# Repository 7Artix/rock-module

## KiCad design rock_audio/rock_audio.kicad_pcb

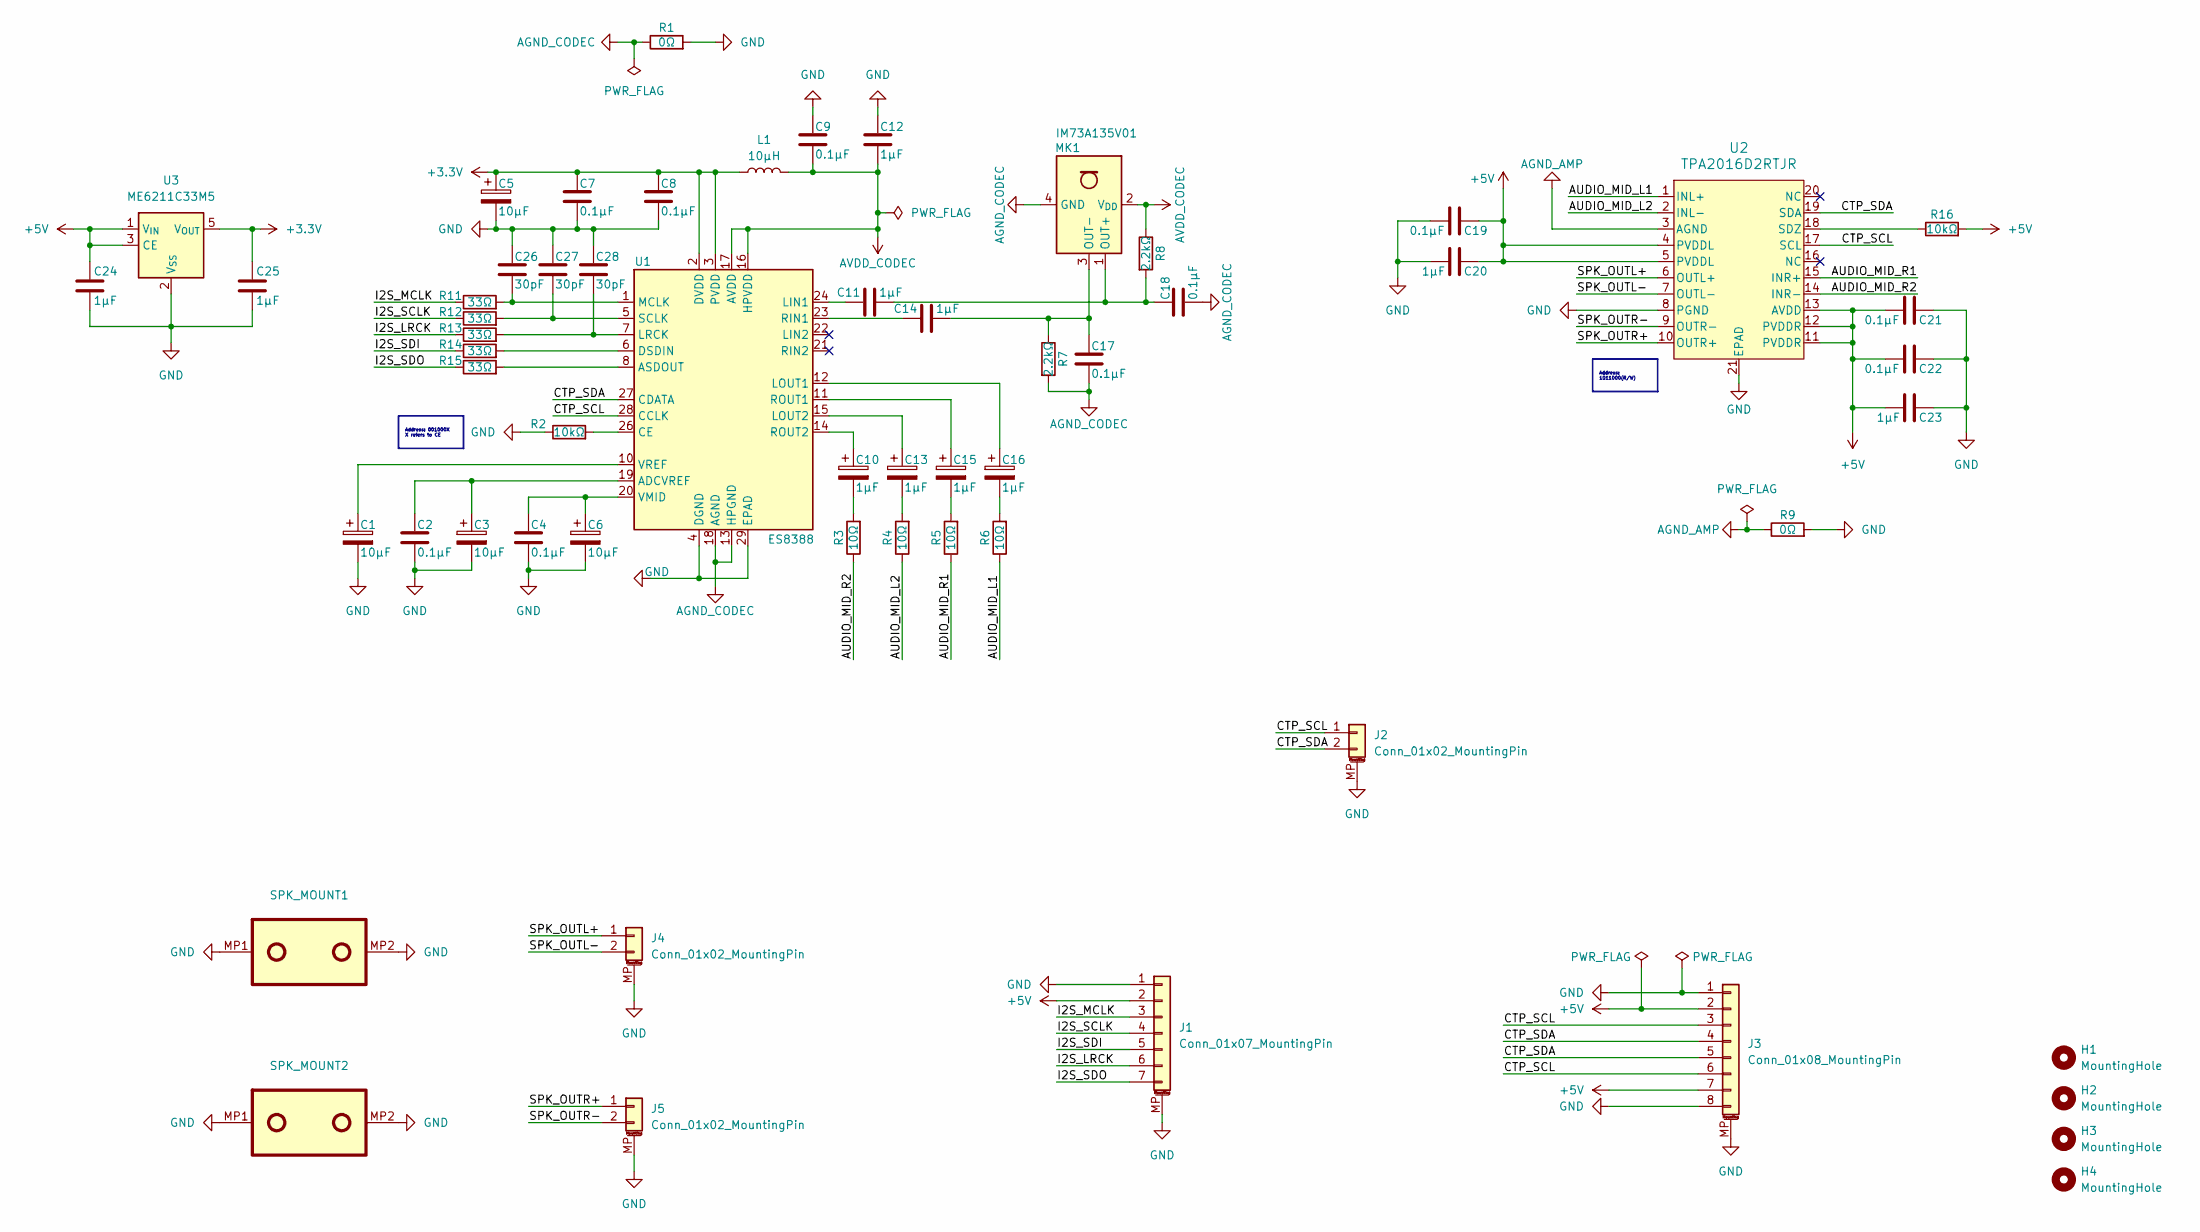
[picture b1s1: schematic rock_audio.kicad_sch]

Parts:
C1, C3, C5, C6: 10μF; CP_EIA-3216-18_Kemet-A
C2, C4, C7, C8, C9, C17, C18, C19, C21, C22: 0.1μF; C_0402_1005Metric
C10, C13, C15, C16: 1μF; CP_EIA-3216-18_Kemet-A
C11, C12, C14, C20, C23, C24, C25: 1μF; C_0402_1005Metric
C26, C27, C28: 30pF; C_0402_1005Metric
H1, H2, H3, H4: MountingHole; MountingHole_2.7mm_M2.5_ISO14580
J1: Conn_01x07_MountingPin; JST_GH_SM07B-GHS-TB_1x07-1MP_P1.25mm_Horizontal
J2: Conn_01x02_MountingPin; JST_GH_SM02B-GHS-TB_1x02-1MP_P1.25mm_Horizontal
J3: Conn_01x08_MountingPin; TE_0-1734839-8_1x08-1MP_P0.5mm_Horizontal
J4, J5: Conn_01x02_MountingPin; MX1.25-2P-H
L1: 10µH; L_Wurth_WE-LQSH-2512
MK1: IM73A135V01; Infineon_PG-LLGA-5-2
R1, R9: 0Ω; R_0603_1608Metric
R2, R16: 10kΩ; R_0402_1005Metric
R3, R4, R5, R6: 10Ω; R_0603_1608Metric
R7, R8: 2.2kΩ; R_0402_1005Metric
R11, R12, R13, R14, R15: 33Ω; R_0402_1005Metric
SPK_MOUNT1, SPK_MOUNT2: SPEAKER_XFDZ_3520
U1: ES8388; QFN-28-1EP_4x4mm_P0.45mm_EP2.6x2.6mm
U2: TPA2016D2RTJR; RTJ20_2P7X2P7
U3: ME6211C33M5; SOT-23-5

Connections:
+3.3V: C5.1, C7.1, C8.1, C25.1, L1.1, U1.2 (DVDD), U1.3 (PVDD), U3.5 (V_{OUT})
+5V: C19.1, C20.1, C21.2, C22.2, C23.2, C24.1, J1.2, J3.2, J3.7, R16.2, U2.4 (PVDDL), U2.5 (PVDDL), U2.11 (PVDDR), U2.12 (PVDDR), U2.13 (AVDD), U3.1 (V_{IN}), U3.3 (CE)
/AUDIO_MID_L1: R6.1, U2.1 (INL+)
/AUDIO_MID_L2: R4.1, U2.2 (INL-)
/AUDIO_MID_R1: R5.1, U2.15 (INR+)
/AUDIO_MID_R2: R3.1, U2.14 (INR-)
/CTP_SCL: J2.1, J3.3, J3.6, U1.28 (CCLK), U2.17 (SCL)
/CTP_SDA: J2.2, J3.4, J3.5, U1.27 (CDATA), U2.19 (SDA)
/I2S_LRCK: J1.6, R13.1
/I2S_MCLK: J1.3, R11.1
/I2S_SCLK: J1.4, R12.1
/I2S_SDI: J1.5, R14.1
/I2S_SDO: J1.7, R15.1
/SPK_OUTL+: J4.1, U2.6 (OUTL+)
/SPK_OUTL-: J4.2, U2.7 (OUTL-)
/SPK_OUTR+: J5.1, U2.10 (OUTR+)
/SPK_OUTR-: J5.2, U2.9 (OUTR-)
AGND_AMP: R9.1, U2.3 (AGND)
AGND_CODEC: C17.2, C18.2, MK1.4 (GND), MK1.5 (GND), R1.1, R7.2, U1.13 (HPGND), U1.18 (AGND)
AVDD_CODEC: C9.2, C12.2, L1.2, MK1.2 (V_{DD}), R8.1, U1.16 (HPVDD), U1.17 (AVDD)
GND: C1.2, C2.2, C3.2, C4.2, C5.2, C6.2, C7.2, C8.2, C9.1, C12.1, C19.2, C20.2, C21.1, C22.1, C23.1, C24.2, C25.2, C26.1, C27.1, C28.1, J1.1, J1.MP (MountPin), J2.MP (MountPin), J3.1, J3.8, J3.MP (MountPin), J4.MP (MountPin), J5.MP (MountPin), R1.2, R2.1, R9.2, SPK_MOUNT1.MP1, SPK_MOUNT1.MP2, SPK_MOUNT2.MP1, SPK_MOUNT2.MP2, U1.4 (DGND), U1.29 (EPAD), U2.8 (PGND), U2.21 (EPAD), U3.2 (V_{SS})
unnamed: C10.2, R3.2
unnamed: C13.2, R4.2
unnamed: C15.2, R5.2
unnamed: C16.2, R6.2
unnamed: C11.2, C18.1, MK1.1 (OUT+), R8.2
unnamed: C14.2, C17.1, MK1.3 (OUT-), R7.1
unnamed: C2.1, C3.1, U1.19 (ADCVREF)
unnamed: R15.2, U1.8 (ASDOUT)
unnamed: R2.2, U1.26 (CE)
unnamed: R14.2, U1.6 (DSDIN)
unnamed: C11.1, U1.24 (LIN1)
unnamed: C16.1, U1.12 (LOUT1)
unnamed: C13.1, U1.15 (LOUT2)
unnamed: C28.2, R13.2, U1.7 (LRCK)
unnamed: C26.2, R11.2, U1.1 (MCLK)
unnamed: C14.1, U1.23 (RIN1)
unnamed: C15.1, U1.11 (ROUT1)
unnamed: C10.1, U1.14 (ROUT2)
unnamed: C27.2, R12.2, U1.5 (SCLK)
unnamed: C4.1, C6.1, U1.20 (VMID)
unnamed: C1.1, U1.10 (VREF)
unnamed: R16.1, U2.18 (SDZ)

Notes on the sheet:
Address: 1011000(R/W)
Address: 001000X X refers to CE

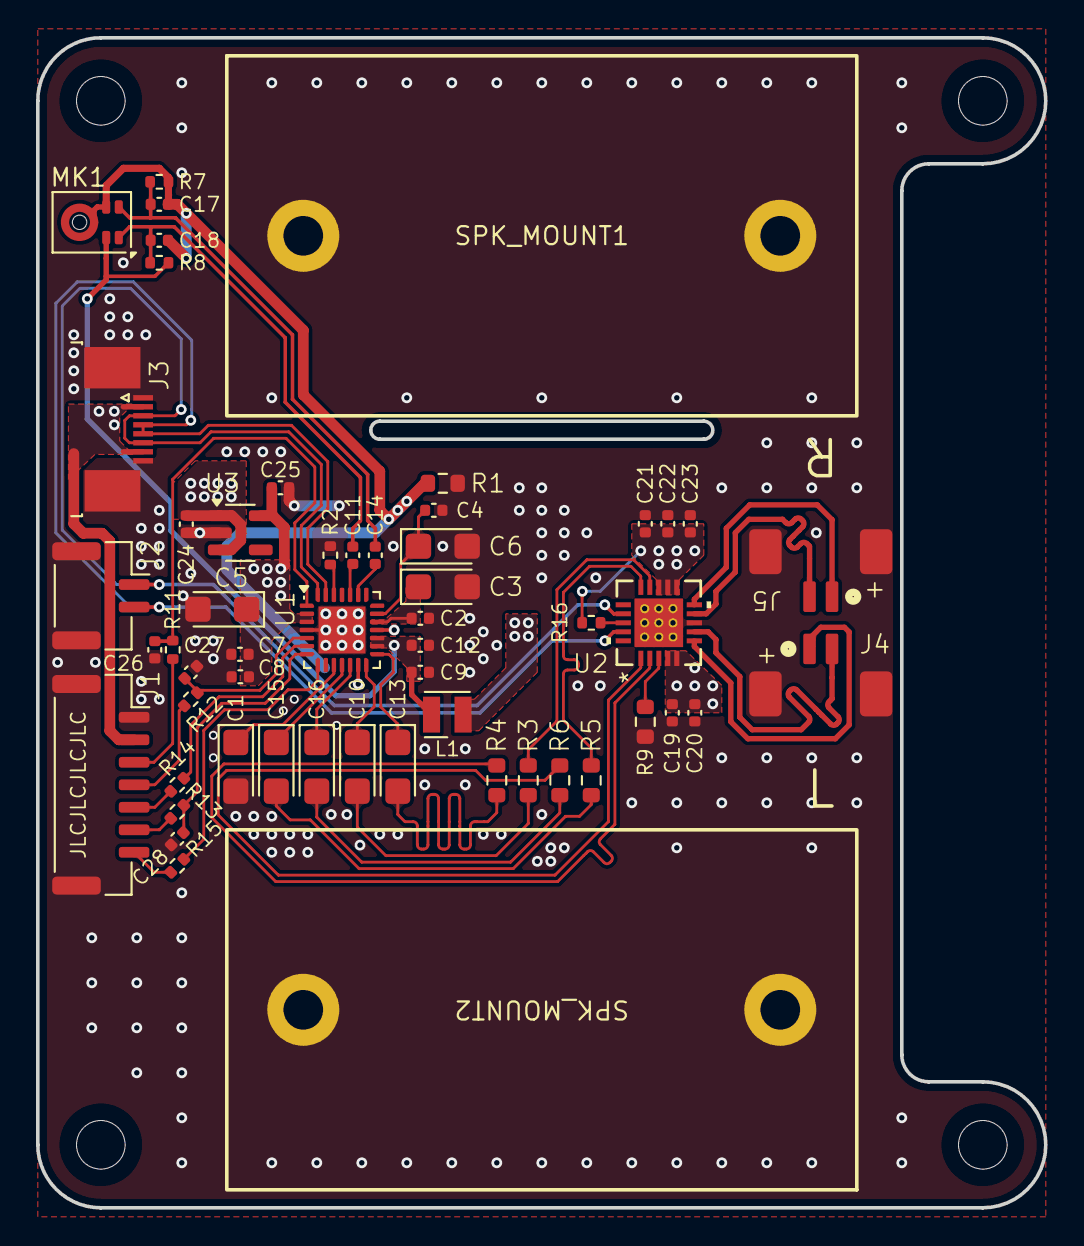
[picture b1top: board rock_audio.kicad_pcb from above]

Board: 2 copper layers, 56.0 x 65.0 mm, 59 parts (0 on the bottom side), 43 nets.

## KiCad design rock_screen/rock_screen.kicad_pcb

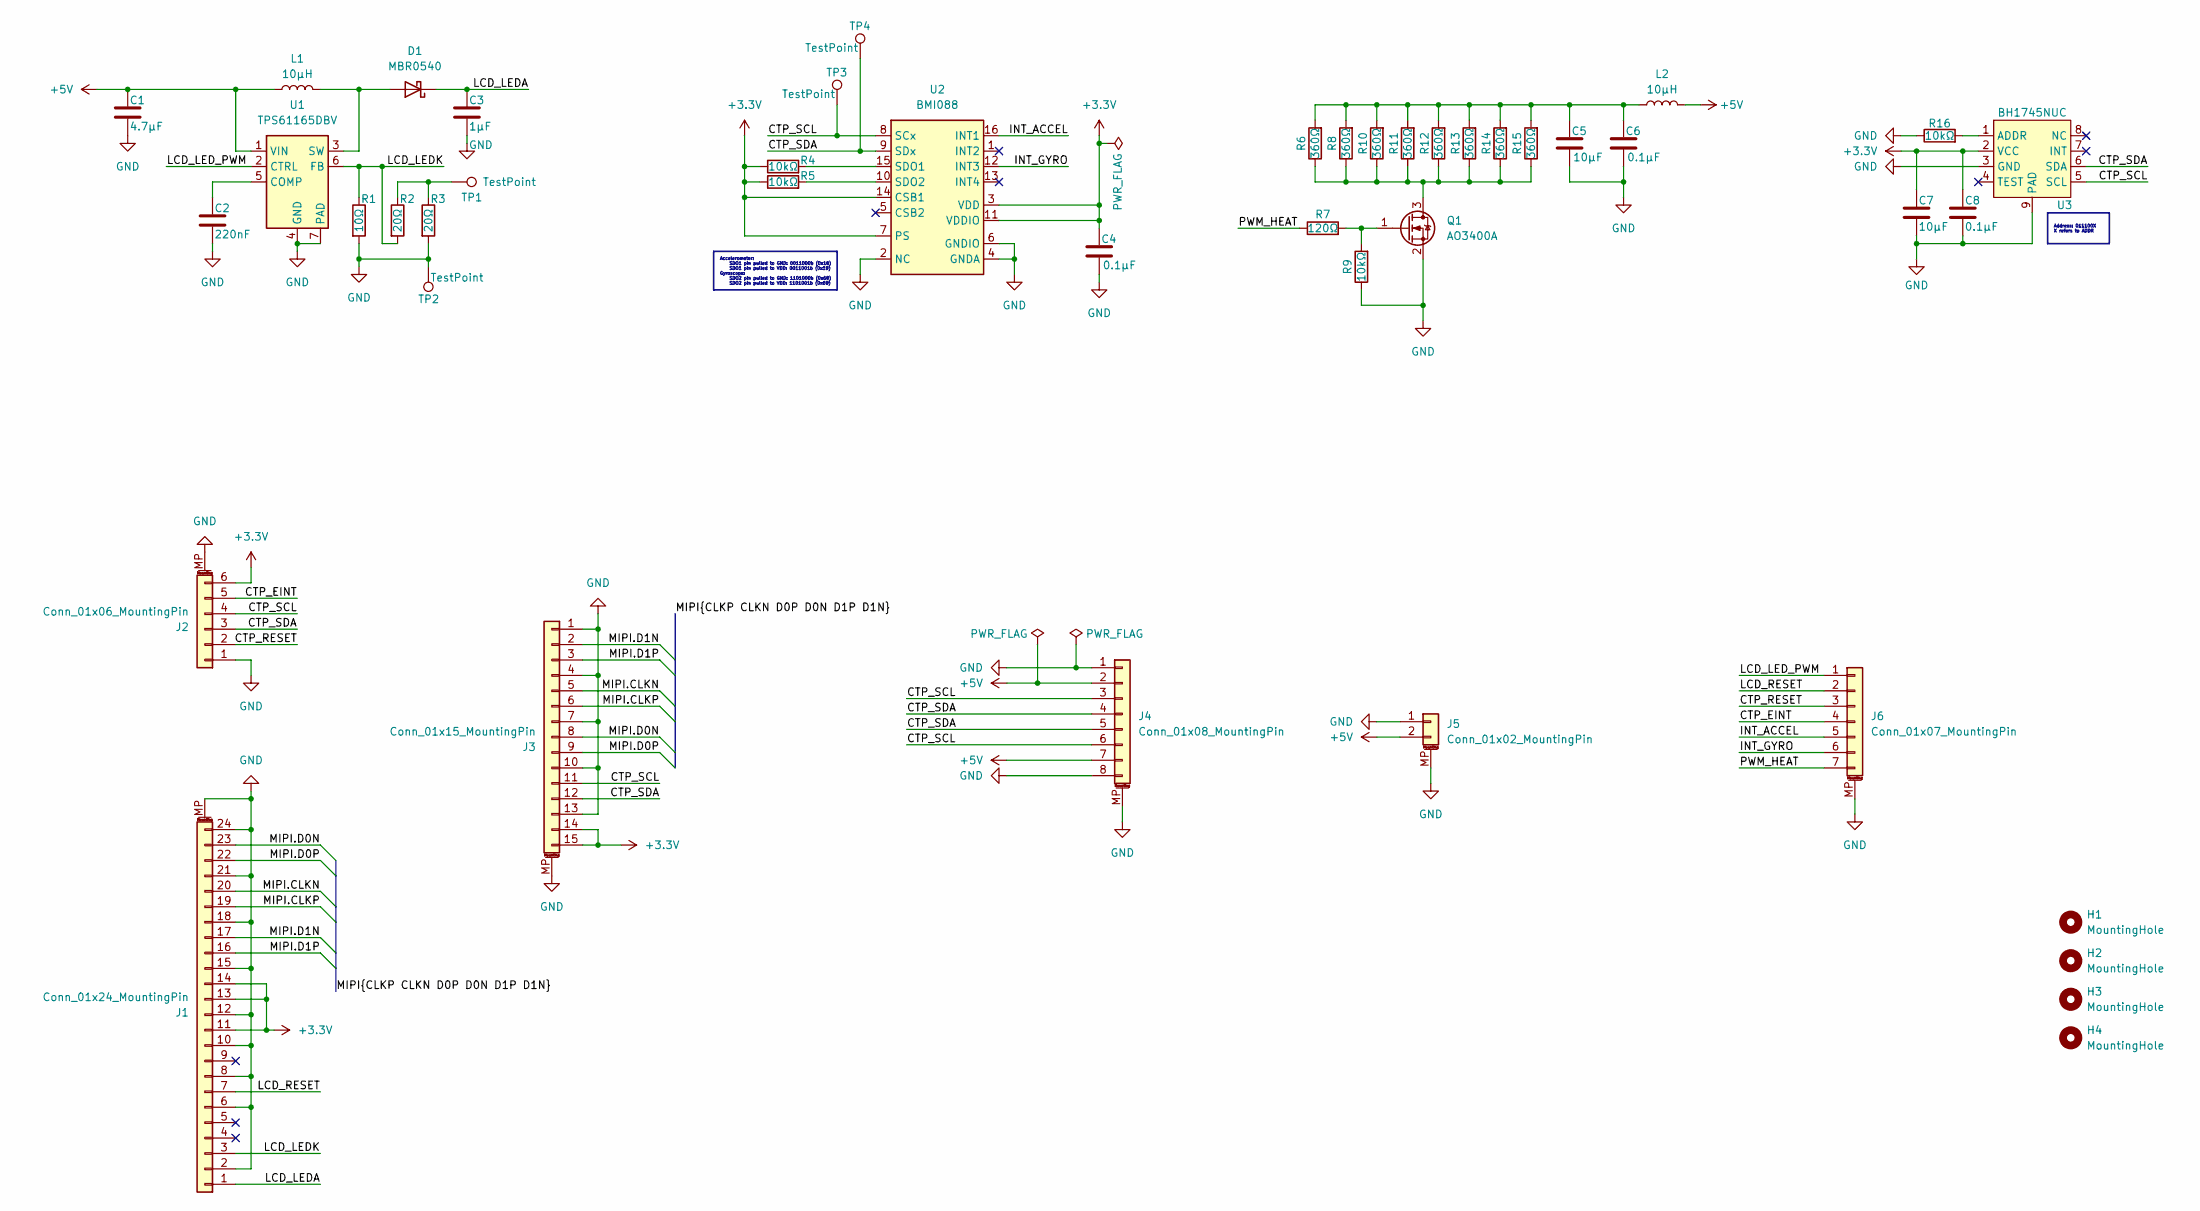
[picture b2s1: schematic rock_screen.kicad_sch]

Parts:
C1: 4.7µF; C_0402_1005Metric
C2: 220nF; C_0402_1005Metric
C3: 1µF; C_0402_1005Metric
C4, C6: 0.1μF; C_0402_1005Metric
C5: 10μF; C_0402_1005Metric
C7: 10µF; C_0402_1005Metric
C8: 0.1µF; C_0402_1005Metric
D1: MBR0540; D_SOD-123
H1, H2, H3, H4: MountingHole; MountingHole_2.7mm_M2.5_ISO14580
J1: Conn_01x24_MountingPin; Jushuo_AFC07-S24FCA-00_1x24-1MP_P0.50_Horizontal
J2: Conn_01x06_MountingPin; Jushuo_AFC07-S06FCA-00_1x6-1MP_P0.50_Horizontal
J3: Conn_01x15_MountingPin; JUSHUO_AFA07-S15FCA-00_1x15-1MP_P1.0mm_Horizontal
J4: Conn_01x08_MountingPin; TE_0-1734839-8_1x08-1MP_P0.5mm_Horizontal
J5: Conn_01x02_MountingPin; JST_GH_SM02B-GHS-TB_1x02-1MP_P1.25mm_Horizontal
J6: Conn_01x07_MountingPin; JST_GH_SM07B-GHS-TB_1x07-1MP_P1.25mm_Horizontal
L1, L2: 10µH; L_Wurth_WE-LQSH-2512
Q1: AO3400A; SOT-23
R1: 10Ω; R_0402_1005Metric
R2, R3: 20Ω; R_0402_1005Metric
R4, R5, R9, R16: 10kΩ; R_0402_1005Metric
R6, R8, R10, R11, R12, R13, R14, R15: 360Ω; R_0402_1005Metric
R7: 120Ω; R_0402_1005Metric
TP1, TP2, TP3, TP4: TestPoint; TestPoint_Pad_D1.0mm
U1: TPS61165DBV; WSON-6-1EP_2x2mm_P0.65mm_EP1x1.6mm_ThermalVias
U2: BMI088; BOSCH_PQFN50P450X300X100_16N
U3: BH1745NUC; WSON-8-1EP_2x2mm_P0.5mm_EP0.9x1.6mm

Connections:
+3.3V: C4.1, C7.1, C8.1, J1.11, J1.13, J1.14, J2.6, J3.14, J3.15, R4.1, R5.1, U2.3 (VDD), U2.7 (PS), U2.11 (VDDIO), U2.14 (CSB1), U3.2 (VCC)
+5V: C1.1, J4.2, J4.7, J5.2, L1.1, L2.2, U1.1 (VIN)
/CTP_EINT: J2.5, J6.4
/CTP_RESET: J2.2, J6.3
/CTP_SCL: J2.4, J3.11, J4.3, J4.6, TP3.1, U2.8 (SCx), U3.5 (SCL)
/CTP_SDA: J2.3, J3.12, J4.4, J4.5, TP4.1, U2.9 (SDx), U3.6 (SDA)
/INT_ACCEL: J6.5, U2.16 (INT1)
/INT_GYRO: J6.6, U2.12 (INT3)
/LCD_LEDA: C3.1, D1.1 (K), J1.1
/LCD_LEDK: J1.3, R1.1, R2.2, U1.6 (FB)
/LCD_LED_PWM: J6.1, U1.2 (CTRL)
/LCD_RESET: J1.7, J6.2
/MIPI.CLKN: J1.20, J3.5
/MIPI.CLKP: J1.19, J3.6
/MIPI.D0N: J1.23, J3.8
/MIPI.D0P: J1.22, J3.9
/MIPI.D1N: J1.17, J3.2
/MIPI.D1P: J1.16, J3.3
/PWM_HEAT: J6.7, R7.1
GND: C1.2, C2.2, C3.2, C4.2, C5.2, C6.2, C7.2, C8.2, J1.2, J1.6, J1.8, J1.10, J1.12, J1.15, J1.18, J1.21, J1.24, J1.MP (MountPin), J2.1, J2.MP (MountPin), J3.1, J3.4, J3.7, J3.10, J3.13, J3.MP (MountPin), J4.1, J4.8, J4.MP (MountPin), J5.1, J5.MP (MountPin), J6.MP (MountPin), Q1.2 (S), R1.2, R3.2, R9.1, R16.1, TP2.1, U1.4 (GND), U1.7 (PAD), U2.2 (NC), U2.4 (GNDA), U2.6 (GNDIO), U3.3 (GND), U3.9 (PAD)
unnamed: C5.1, C6.1, L2.1, R6.2, R8.2, R10.2, R11.2, R12.2, R13.2, R14.2, R15.2
unnamed: D1.2 (A), L1.2, U1.3 (SW)
unnamed: Q1.3 (D), R6.1, R8.1, R10.1, R11.1, R12.1, R13.1, R14.1, R15.1
unnamed: Q1.1 (G), R7.2, R9.2
unnamed: R2.1, R3.1, TP1.1
unnamed: C2.1, U1.5 (COMP)
unnamed: R4.2, U2.15 (SDO1)
unnamed: R5.2, U2.10 (SDO2)
unnamed: R16.2, U3.1 (ADDR)

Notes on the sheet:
Address: 011100X X refers to ADDR
Accelerometer: SDO1 pin pulled to GND: 0011000b (0x18) SDO1 pin pulled to VDD: 0011001b (0x19) Gyroscope: SDO2 pin pulled to GND: 1101000b (0x68) SDO2 pin pulled to VDD: 1101001b (0x69)

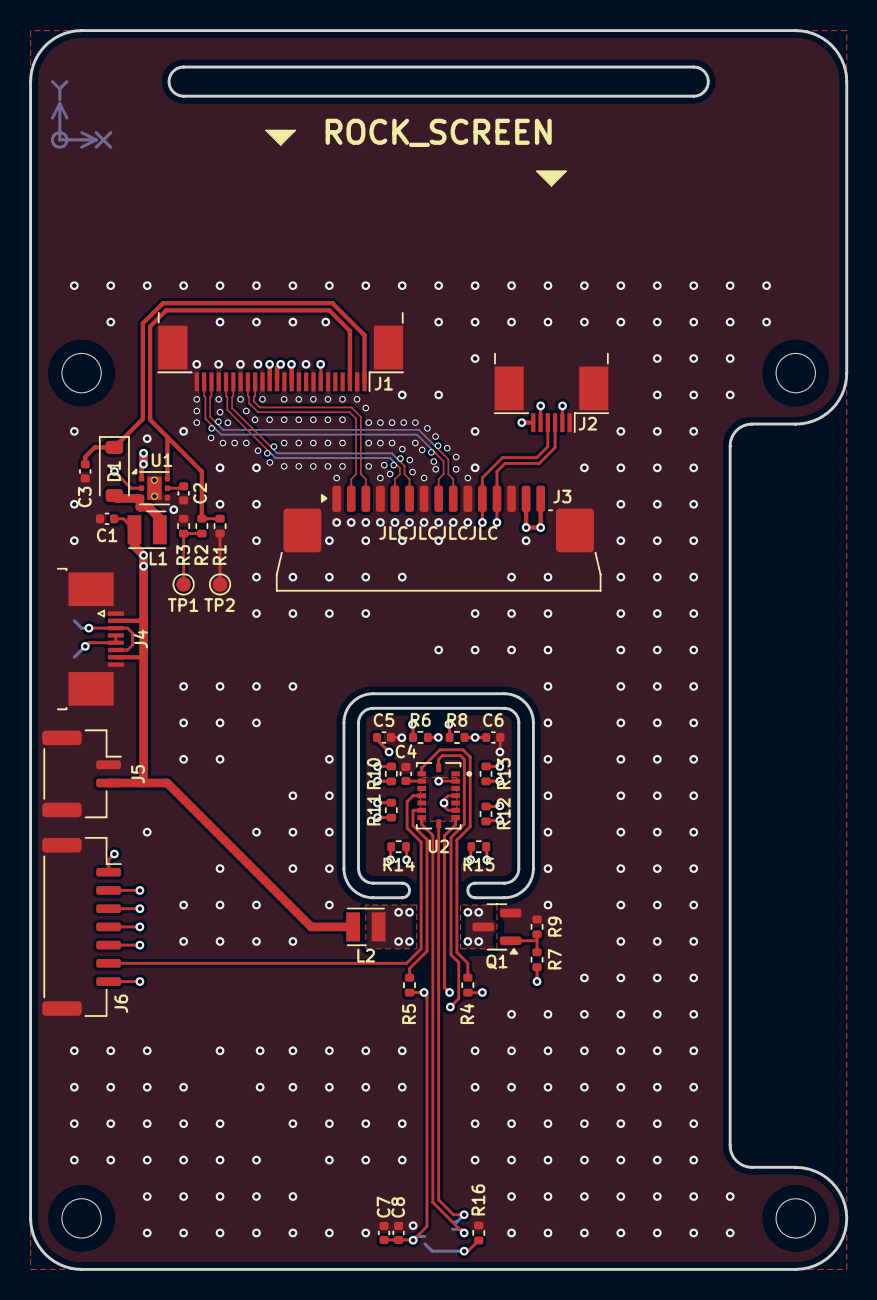
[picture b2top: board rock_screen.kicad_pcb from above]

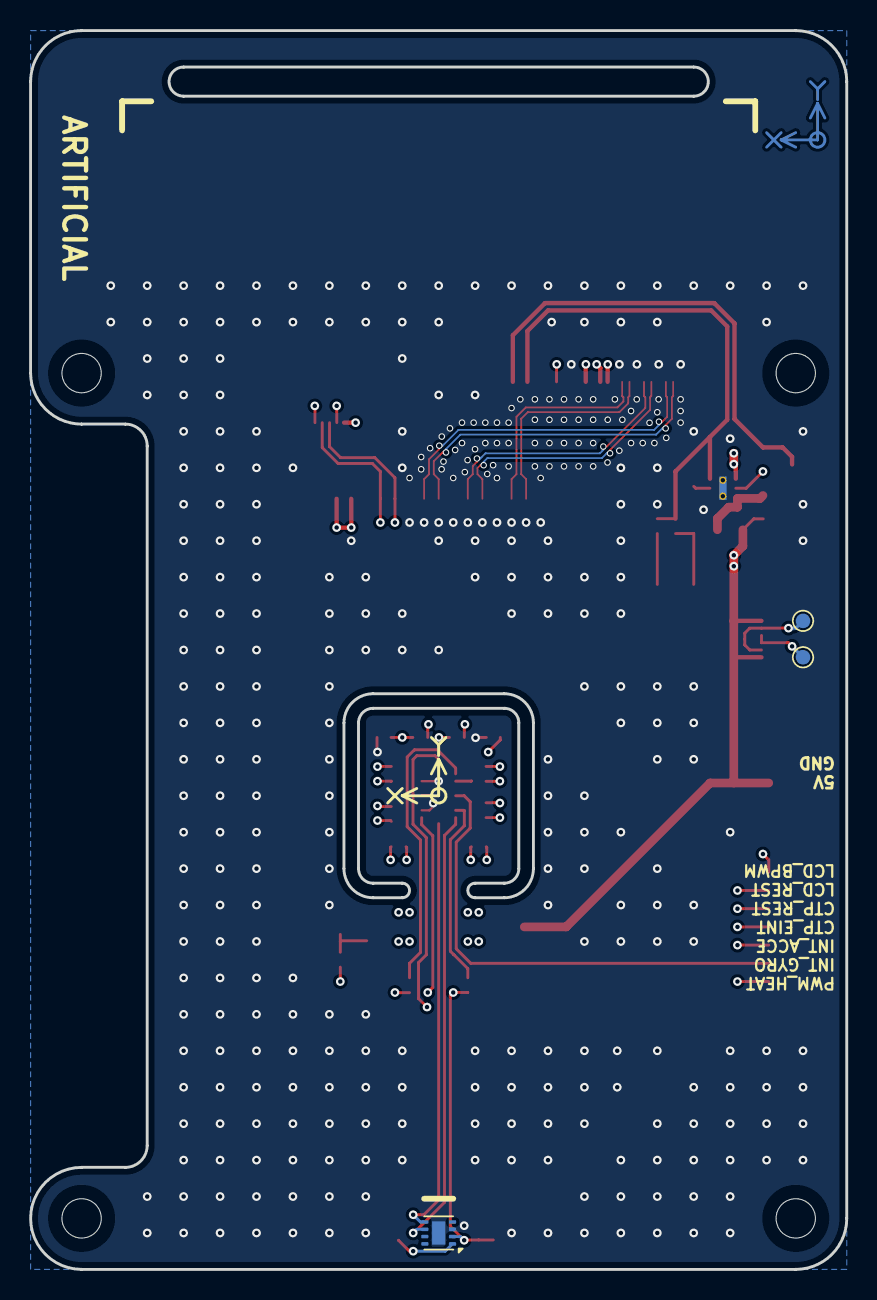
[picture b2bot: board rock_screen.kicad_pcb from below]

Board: 4 copper layers, 56.0 x 85.0 mm, 45 parts (3 on the bottom side), 29 nets.
